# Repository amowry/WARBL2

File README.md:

## WARBL2 is an open-source USB MIDI and BLE MIDI wind controller.

Please see the web site for more info:

https://warbl.xyz

To power the WARBL on, plug into USB or click button 3 (lowest button).

To manually power off the WARBL while under battery power, you can click the reset button (or use a button action assigned in the Configuration Tool, which by default is a long-press of button 3).

For updating the firmware, typical users would just hold down button 1 while plugging the WARBL in to USB and then drag/drop the supplied .uf2 file to the drive named WARBLBOOT. If the WARBL is already plugged in, you can also double-click the reset button to enter the bootloader mode. The most recent flash.uf2 file is located in the build/adafruit.nrf52.warbl2 directory.
 
Advanced users can use the Arduino IDE to modify and upload the code. Modify the code at your own risk and note that while modifying the battery management code won't have dangerous results it could result in reducing the lifespan of the battery.

### How to use WARBL2 with the Arduino IDE:

#### Install Arduino IDE

* Install / run the latest version of the Arduino IDE. [You can download the latest version of the Arduino IDE here](https://www.arduino.cc/en/Main/Software).

* In Linux, the Arduino IDE requires that you be part of the `dialout` group to successfully detect and write to hardware (see [here](https://support.arduino.cc/hc/en-us/articles/4401874331410#ser_open-permission-denied)). If running `id` in a terminal does not list `dialout` as one of the groups your user belongs to, [run `sudo usermod -a -G dialout $USER`](https://support.arduino.cc/hc/en-us/articles/360016495679-Fix-port-access-on-Linux), then log out and back in. Running `id` should now include the `dialout` group.

#### Editing and uploading the WARBL firmware

*  I used the Adafruit ItsyBitsy NRF52840 Express for prototyping WARBL, so the easiest way to set up the IDE is to install the Adafruit boards package, [following the instructions here](https://learn.adafruit.com/adafruit-itsybitsy-nrf52840-express/arduino-support-setup).

* Download the WARBL2 code from this repository (I recommend using the most recent *release* code, *NOT* the current main branch), and move the boards.local.txt file from the "firmware" directory into the directory on your machine that contains the boards.txt file for the Adafruit NR52 boards, typically found here:
   
   * Windows: `C:\Users\(username)\AppData\Local\Arduino15\packages\adafruit\hardware\nrf52\1.6.0` 
   
   * Linux: `/home/(username)/.arduino15/packages/adafruit/hardware/nrf52/1.6.0`
     
   * Mac: ` ~/LibraryArduino15/packages/adafruit/hardware/nrf52/1.5.0/`

*	Now open the warbl2_firmware.ino sketch that you saved in your sketchbook folder.
  
*	In the Tools menu select: Board: > Adafruit nRF52 > WARBL2

*	Next, you’ll need to install libraries included in the sketch that aren’t installed by default. To install them, go to Sketch > Include Library > Manage Libraries, then search for the name of each, one at a time. Then it will give you an option to install each one.

*	Then turn on “show verbose ouput" for both "compile" and "upload" under File > Preferences. Now, click the upload button and check that it compiles without errors. 

*	Then, when it tries to upload, you should see this message at the bottom of the screen:

`Waiting for upload port...`

*	IF the WARBL currently has a "Release" version of the firmware (see below), you'll then have to use a toothpick to double-click the reset button to enter programming mode. The LED pulse in blue and the code should upload, which will take several seconds. If the LED doesn’t light or blinks rapidly, try again. If the IDE stops trying to upload, click “Upload” again, and try double-clicking again. It can take a few tries to get the timing right. If you've loaded a non-release version then the serial CDC port will be active and the firmware upload should proceed without having to first double-click the reset button.

### A few additional notes:
The serial CDC class on WARBL needs to be turned off to make it a USB MIDI class-compliant device. This also means that you won't be able to use the serial monitor in Arduino IDE, and you'll have to double-click the programming button to install firmware (as described above). To turn serial back on, you can comment out the following line in the sketch:

`#define RELEASE //Uncomment for release version (turns off CDC)`

Turning on CDC makes it easier to debug and makes it so uploads should proceed automatically.

Have fun!

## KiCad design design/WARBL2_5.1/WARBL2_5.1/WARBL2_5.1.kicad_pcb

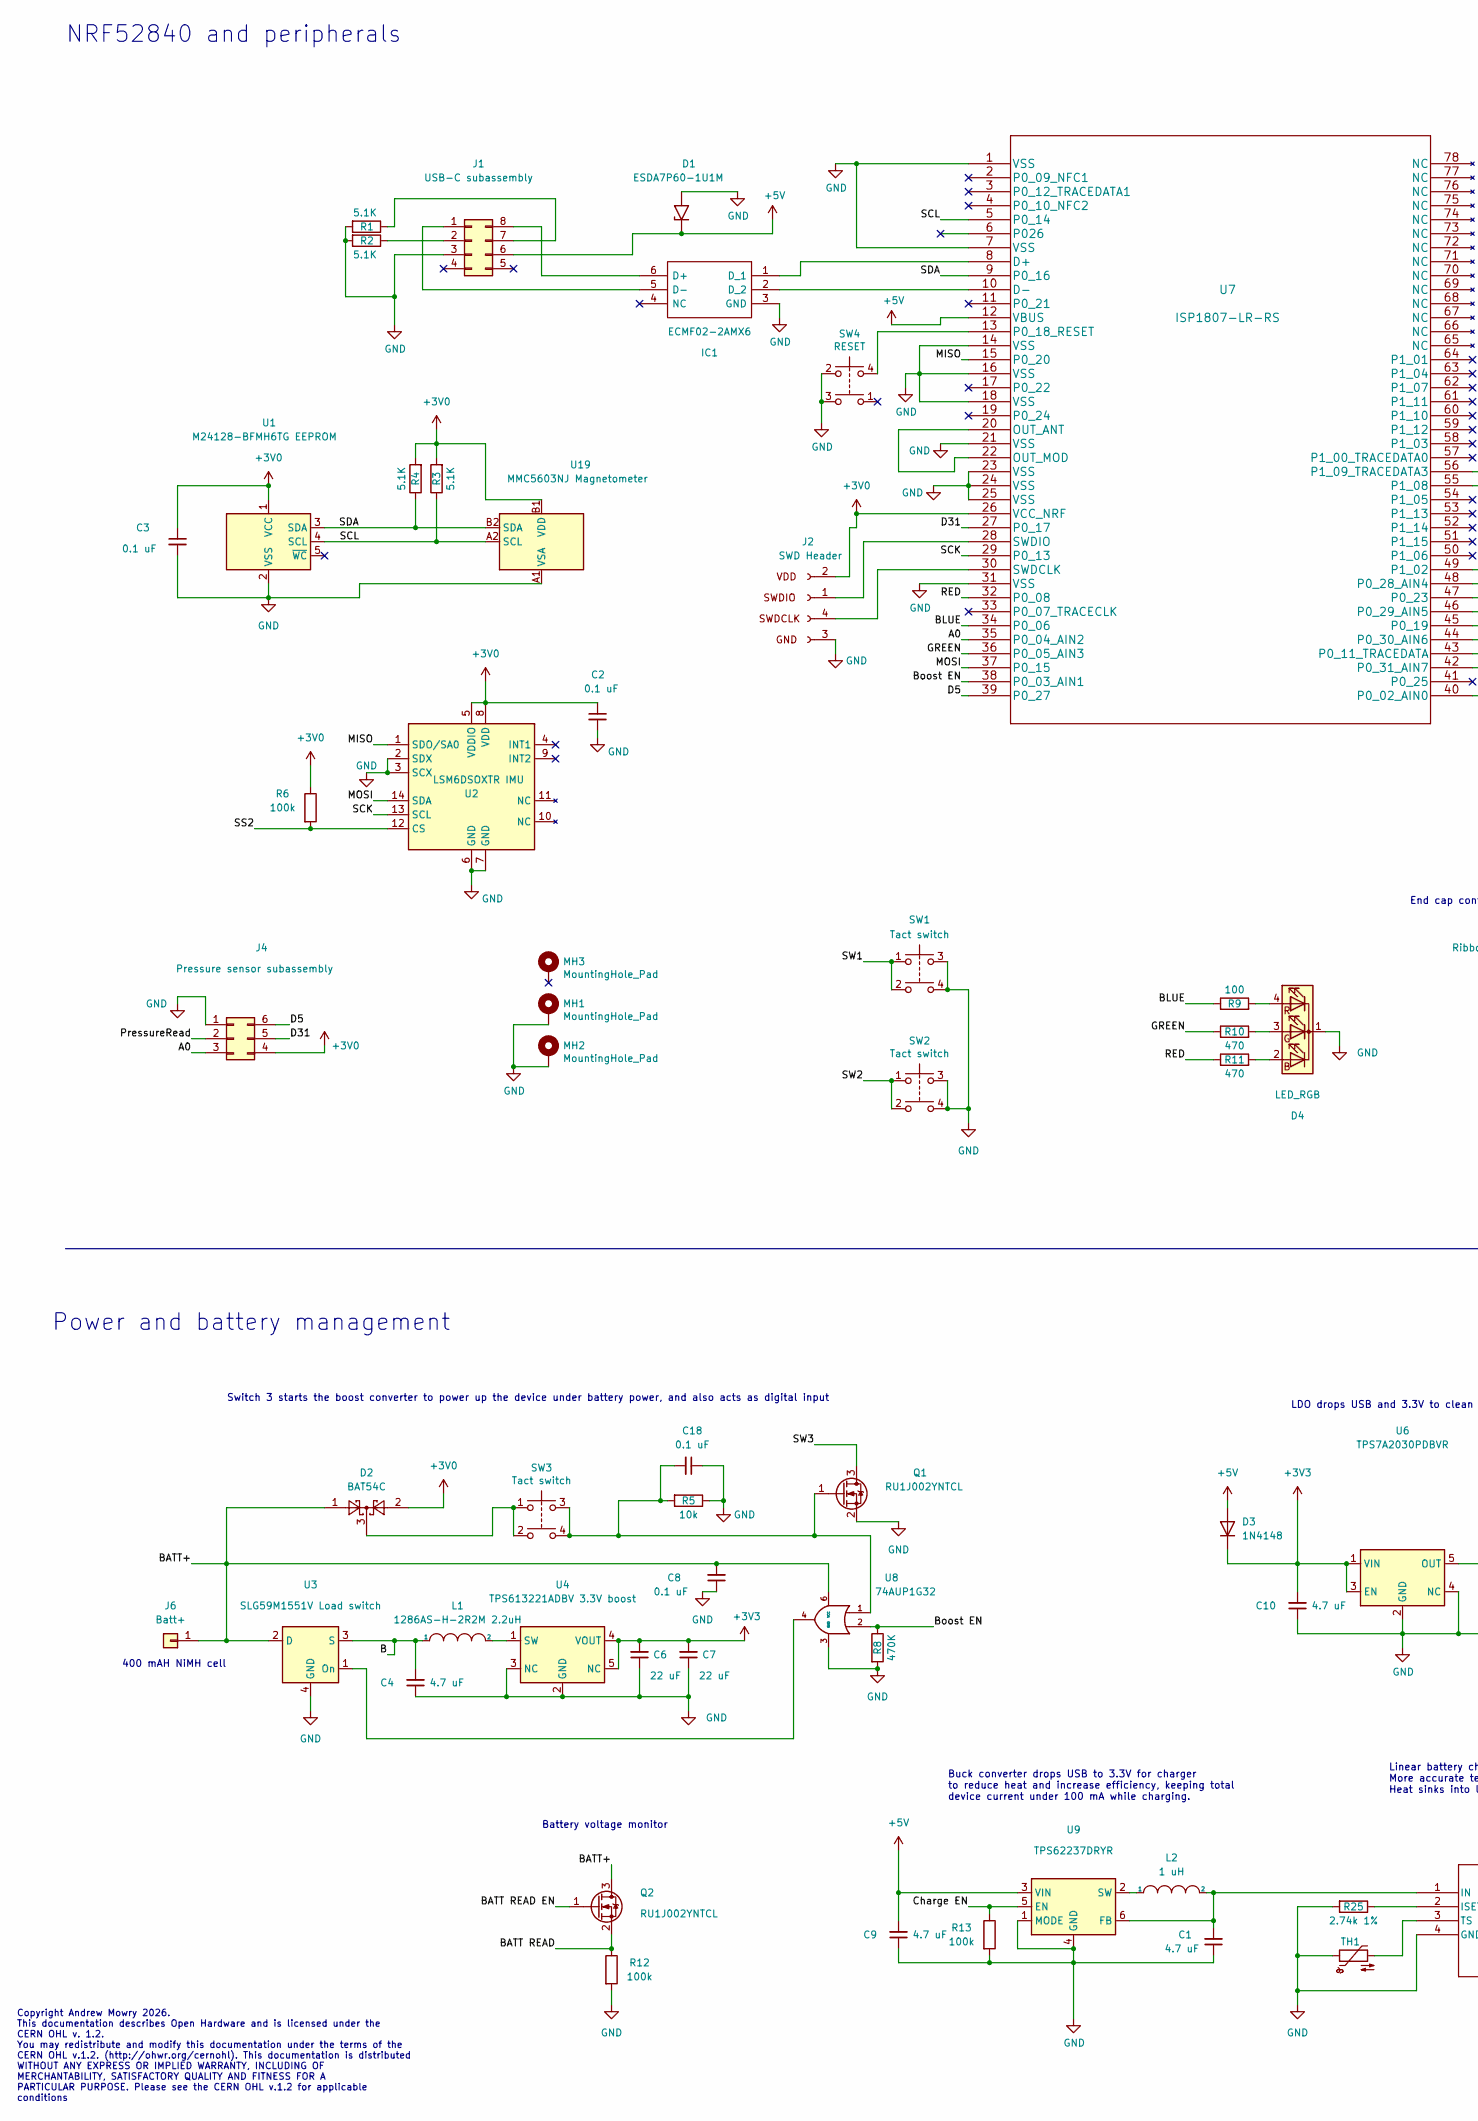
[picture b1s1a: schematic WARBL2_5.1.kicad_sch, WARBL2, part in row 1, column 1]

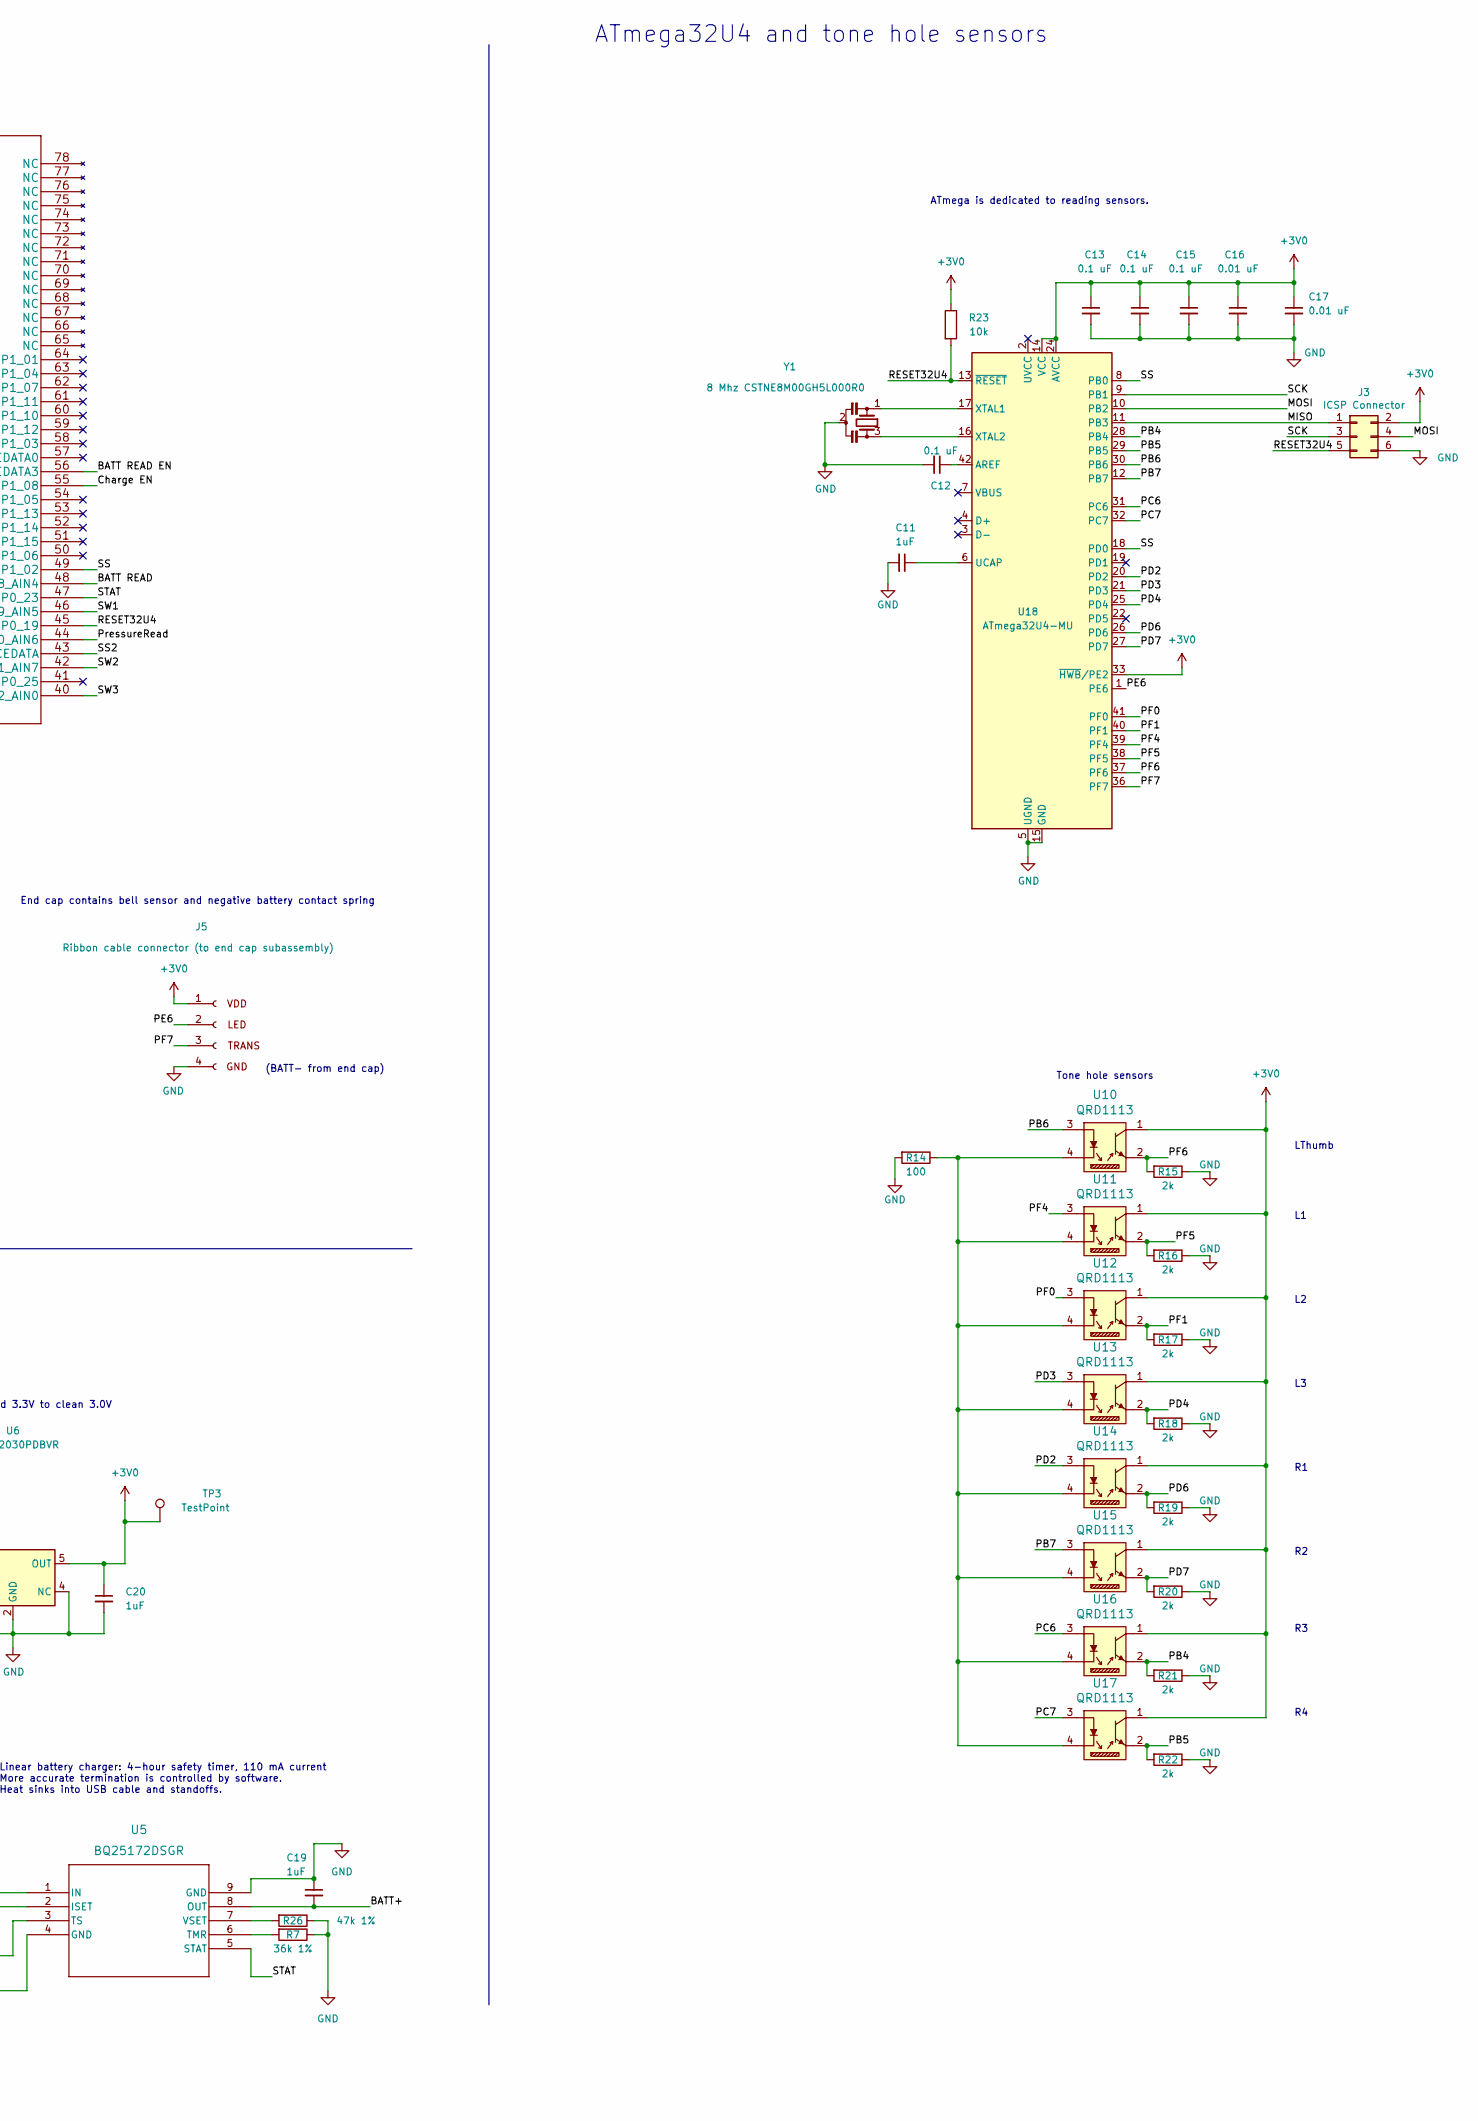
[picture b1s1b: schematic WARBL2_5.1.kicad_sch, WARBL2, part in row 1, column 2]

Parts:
C1, C4, C9, C10: 4.7 uF; C_0603_1608Metric; Mfg Part # C1608X7S1A475K080AC; Digi-Key_PN 445-14258-2-ND
C2, C3, C8, C12, C13, C14, C15, C18: 0.1 uF; C_0603_1608Metric; Mfg Part # CL10F104ZB8NNNC; Digi-Key_PN 1276-1012-2-ND
C6, C7: 22 uF; C_0603_1608Metric; Mfg Part # C1608X5R1A226M080AC; Digi-Key_PN 445-9077-2-ND
C11, C19, C20: 1uF; C_0603_1608Metric; Mfg Part # CL10B105KP8NNNC; Digi-Key_PN 1276-1946-2-ND
C16, C17: 0.01 uF; C_0603_1608Metric; Mfg Part # CL10B103KB8NNNC; Digi-Key_PN 1276-1009-2-ND
D1: ESDA7P60-1U1M; ESDA7P601U1M; Mfg Part # ESDA7P60-1U1M; Digi-Key_PN 497-16253-2-ND
D2: BAT54C; SOT-23; Mfg Part # BAT54C; Digi-Key_PN 1655-BAT54CTR-ND
D3: 1N4148; D_SOD-323; Mfg Part # 1N4148WS; Digi-Key_PN 1655-1N4148WSTR-ND
D4: LED_RGB; LED_LiteOn_LTST-C19HE1WT; Mfg Part # APTF1616SEJ3ZGGVBDC; Digi-Key_PN 754-2166-2-ND
IC1: ECMF02-2AMX6; QFN-6L_STM; Mfg Part # ECMF02-2AMX6; Digi-Key_PN 497-10773-2-ND
J1: USB-C subassembly; PinHeader_2x04_P2.54mm_Vertical; JLCPCB BOM 0
J2: SWD Header; PinHeader_1x04_P2.54mm_Vertical_SMD_Pin1Left; JLCPCB BOM 0
J3: ICSP Connector; SMD_ICSPHeader_Pitch2.54mm; JLCPCB BOM 0
J4: Pressure sensor subassembly; ABPLLND060MGAA3_largepads; JLCPCB BOM 0
J5: Ribbon cable connector (to end cap subassembly); PinHeader_1x04_P2.00mm_Vertical; JLCPCB BOM 0
J6: Batt+; PinHeader_1x01_P1.00mm_Vertical; JLCPCB BOM 0
L1: 1286AS-H-2R2M 2.2uH; INDC2016X120N; Mfg Part # 1286AS-H-2R2M=P2; Digi-Key_PN 490-10605-2-ND
L2: 1 uH; L_0603_1608Metric; Mfg Part # LQM18PZ1R0MCHD; Digi-Key_PN 490-15979-2-ND
MH1, MH2, MH3: MountingHole_Pad; MountingHole__2_56_Pad_small; JLCPCB BOM 0
Q1, Q2: RU1J002YNTCL; SOT-323_SC-70; Mfg Part # RU1J002YNTCL; Digi-Key_PN RU1J002YNTCLTR-ND
R1, R2, R3, R4: 5.1K; R_0603_1608Metric; Mfg Part # ERJ-3EKF5101V; Digi-Key_PN P5.10KHTR-ND
R5, R23: 10k; R_0603_1608Metric; Mfg Part # ERJ-3GEYJ103V; Digi-Key_PN P10KGTR-ND
R6, R12, R13: 100k; R_0603_1608Metric; Mfg Part # ERJ-3GEYJ104V; Digi-Key_PN P100KGTR-ND
R7: 36k 1%; R_0603_1608Metric; Mfg Part # ERJ-3EKF3602V; Digi-Key_PN P36.0KHTR-ND
R8: 470K; R_0603_1608Metric; Mfg Part # ERJ-3GEYJ474V; Digi-Key_PN P470KGTR-ND
R9, R14: 100; R_0603_1608Metric; Mfg Part # ERJ-3GEYJ101V; Digi-Key_PN P100GTR-ND
R10, R11: 470; R_0603_1608Metric; Mfg Part # ERJ-3GEYJ471V; Digi-Key_PN P470GTR-ND
R15, R16, R17, R18, R19, R20, R21, R22: 2k; R_0603_1608Metric; Mfg Part # ERJ-3GEYJ202V; Digi-Key_PN P2.0KGTR-ND
R25: 2.74k 1%; R_0603_1608Metric; Mfg Part # ERJ-3EKF2741V; Digi-Key_PN P2.74KHTR-ND
R26: 47k 1%; R_0603_1608Metric; Mfg Part # ERJ-3EKF4702V; Digi-Key_PN P47.0KHTR-ND
SW1, SW2, SW3: Tact switch; TL3305BF160QG; Mfg Part # PTS647SM50SMTR2LFSTR-ND; Digi-Key_PN PTS647SM50SMTR2LFSTR-ND
SW4: RESET; SW_KMR221GLFS; Mfg Part # KMR211GLFS; Digi-Key_PN 401-1426-2-ND
TH1: NCU18XH103F60RB; R_0603_1608Metric; Mfg Part # NCU18XH103F60RB; Digi-Key_PN 2259-TH11-3H103FTTR-ND
TP3: TestPoint; TestPoint_Pad_D1.0mm; JLCPCB BOM 0
U1: M24128-BFMH6TG EEPROM; UFDFPN5_1P7X1P4_STM; Mfg Part # M24128-BFMH6TG; Digi-Key_PN 497-17565-2-ND
U2: LSM6DSOXTR IMU; LGA-14L_2P5X3X0P83_STM; Mfg Part # LSM6DSOXTR; Digi-Key_PN 497-18367-2-ND
U3: SLG59M1551V Load switch; VLGA-4_2x2.5mm_P1.65mm; Mfg Part # SLG59M1551V; Digi-Key_PN 1827-1074-2-ND
U4: TPS613221ADBV 3.3V boost; DBV0005A_L; Mfg Part # TPS613221ADBVT; Digi-Key_PN 296-49467-2-ND
U5: BQ25172DSGR; WSON8_DSG008A_BQ_TEX; Mfg Part # BQ25172DSGR; Digi-Key_PN 296-BQ25172DSGRTR-ND
U6: TPS7A2030PDBVR; DBV0005A_L; Mfg Part # TPS7A2030PDBVR; Digi-Key_PN 296-TPS7A2030PDBVRTR-ND
U7: ISP1807-LR-RS; Mfg Part # ISP1807-LR-RS; Digi-Key_PN 1786-1019-2-ND
U8: 74AUP1G32; DSF6; Mfg Part # SN74AUP1G32DSFR; Digi-Key_PN 296-27310-2-ND
U9: TPS62237DRYR; DRY0006A; Mfg Part # TPS62237DRYR; Digi-Key_PN 296-39454-2-ND
U10, U11, U12, U13, U14, U15, U16, U17: QRD1113; Reflective_Sensor_QRD1114; Digi-Key_PN QRD1113
U18: ATmega32U4-MU; QFN-44-1EP_7x7mm_P0.5mm_EP5.2x5.2mm; Mfg Part # ATMEGA32U4-MUR; Digi-Key_PN ATMEGA32U4-MURTR-ND
U19: MMC5603NJ Magnetometer; WLP-4_0.86x0.86mm_P0.4mm
Y1: 8 Mhz CSTNE8M00GH5L000R0; CSTNE8M00GH5L000R0_MUR; Mfg Part # CSTNE8M00GH5L000R0; Digi-Key_PN 490-17962-2-ND

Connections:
+3V0: C2.1, C3.1, C13.1, C14.1, C15.1, C16.1, C17.1, C20.1, D2.2, J2.2 (VDD), J3.2, J4.4, J5.1 (VDD), R3.2, R4.2, R6.1, R23.1, TP3.1, U1.1 (VCC), U2.5 (VDDIO), U2.8 (VDD), U6.5 (OUT), U7.26 (VCC_NRF), U10.1, U11.1, U12.1, U13.1, U14.1, U15.1, U16.1, U17.1, U18.14 (VCC), U18.24 (AVCC), U18.33 (~HWB/PE2), U18.34 (VCC), U18.44 (AVCC), U19.B1 (VDD)
+3V3: C6.2, C7.2, C10.2, D3.1 (K), U4.4 (VOUT), U4.5 (NC), U6.1 (VIN), U6.3 (EN)
+5V: C9.2, D1.1 (A1), D3.2 (A), J1.6, U7.12 (VBUS), U9.3 (VIN)
/A0: J4.3, U7.35 (P0_04_AIN2)
/B: C4.2, L1.1, U3.3 (S)
/BATT READ: Q2.2 (S), R12.1, U7.48 (P0_28_AIN4)
/BATT READ EN: Q2.1 (G), U7.56 (P1_09_TRACEDATA3)
/BATT+: C8.2, C19.2, D2.1, J6.1, Q2.3 (D), U3.2 (D), U5.8 (OUT), U8.6 (VCC)
/BLUE: R9.1, U7.34 (P0_06)
/Boost EN: R8.1, U7.38 (P0_03_AIN1), U8.2
/Charge EN: R13.1, U7.55 (P1_08), U9.5 (EN)
/D5: J4.6, U7.39 (P0_27)
/D31: J4.5, U7.27 (P0_17)
/GREEN: R10.1, U7.36 (P0_05_AIN3)
/MISO: J3.1, U2.1 (SDO/SA0), U7.15 (P0_20), U18.11 (PB3)
/MOSI: J3.4, U2.14 (SDA), U7.37 (P0_15), U18.10 (PB2)
/PB4: R21.2, U16.2, U18.28 (PB4)
/PB5: R22.2, U17.2, U18.29 (PB5)
/PB6: U10.3, U18.30 (PB6)
/PB7: U15.3, U18.12 (PB7)
/PC6: U16.3, U18.31 (PC6)
/PC7: U17.3, U18.32 (PC7)
/PD2: U14.3, U18.20 (PD2)
/PD3: U13.3, U18.21 (PD3)
/PD4: R18.2, U13.2, U18.25 (PD4)
/PD6: R19.2, U14.2, U18.26 (PD6)
/PD7: R20.2, U15.2, U18.27 (PD7)
/PE6: J5.2 (SWDIO), U18.1 (PE6)
/PF0: U12.3, U18.41 (PF0)
/PF1: R17.2, U12.2, U18.40 (PF1)
/PF4: U11.3, U18.39 (PF4)
/PF5: R16.2, U11.2, U18.38 (PF5)
/PF6: R15.2, U10.2, U18.37 (PF6)
/PF7: J5.3 (SWDCLK), U18.36 (PF7)
/PressureRead: J4.2, U7.44 (P0_30_AIN6)
/RED: R11.1, U7.32 (P0_08)
/RESET32U4: J3.5, R23.2, U7.45 (P0_19), U18.13 (~RESET)
/SCK: J3.3, U2.13 (SCL), U7.29 (P0_13), U18.9 (PB1)
/SCL: R3.1, U1.4 (SCL), U7.5 (P0_14), U19.A2 (SCL)
/SDA: R4.1, U1.3 (SDA), U7.9 (P0_16), U19.B2 (SDA)
/SS: U7.49 (P1_02), U18.8 (PB0), U18.18 (PD0)
/SS2: R6.2, U2.12 (CS), U7.43 (P0_11_TRACEDATA)
/STAT: U5.5 (STAT), U7.47 (P0_23)
/SW1: SW1.1, SW1.2, U7.46 (P0_29_AIN5)
/SW2: SW2.1, SW2.2, U7.42 (P0_31_AIN7)
/SW3: Q1.3 (D), U7.40 (P0_02_AIN0)
GND: C1.1, C2.2, C3.2, C4.1, C6.1, C7.1, C8.1, C9.1, C10.1, C11.2, C12.2, C13.2, C14.2, C15.2, C16.2, C17.2, C18.1, C19.1, C20.2, D1.2 (A2), D4.1 (K), IC1.3 (GND), J1.3, J2.3 (GND), J3.6, J4.1, J5.4 (GND), MH1.1, MH2.1, Q1.2 (S), R1.2, R2.2, R5.1, R7.1, R8.2, R12.2, R13.2, R14.2, R15.1, R16.1, R17.1, R18.1, R19.1, R20.1, R21.1, R22.1, R25.2, R26.1, SW1.3, SW1.4, SW2.3, SW2.4, SW4.2, SW4.3, TH1.1, U1.2 (VSS), U2.2 (SDX), U2.3 (SCX), U2.6 (GND), U2.7 (GND), U3.4 (GND), U4.2 (GND), U4.3 (NC), U5.4 (GND), U5.9 (GND), U6.2 (GND), U6.4 (NC), U7.1 (VSS), U7.7 (VSS), U7.14 (VSS), U7.16 (VSS), U7.18 (VSS), U7.21 (VSS), U7.23 (VSS), U7.24 (VSS), U7.25 (VSS), U7.31 (VSS), U8.3 (GND), U9.1 (MODE), U9.4 (GND), U18.5 (UGND), U18.15 (GND), U18.23 (GND), U18.35 (GND), U18.43 (GND), U18.45 (GND), U19.A1 (VSA), Y1.2
unnamed: C1.2, L2.2, U5.1 (IN), U9.6 (FB)
unnamed: C11.1, U18.6 (UCAP)
unnamed: C12.1, U18.42 (AREF)
unnamed: C18.2, Q1.1 (G), R5.2, SW3.3, SW3.4, U8.1
unnamed: D2.3, SW3.1, SW3.2
unnamed: D4.2 (BA), R11.2
unnamed: D4.3 (GA), R10.2
unnamed: D4.4 (RA), R9.2
unnamed: IC1.1 (D_1), U7.8 (D+)
unnamed: IC1.2 (D_2), U7.10 (D-)
unnamed: IC1.5 (D-), J1.1
unnamed: IC1.6 (D+), J1.8
unnamed: J1.2, R2.1
unnamed: J1.7, R1.1
unnamed: J2.1 (SWDIO), U7.28 (SWDIO)
unnamed: J2.4 (SWDCLK), U7.30 (SWDCLK)
unnamed: L1.2, U4.1 (SW)
unnamed: L2.1, U9.2 (SW)
unnamed: R7.2, U5.6 (TMR)
unnamed: R14.1, U10.4, U11.4, U12.4, U13.4, U14.4, U15.4, U16.4, U17.4
unnamed: R25.1, U5.2 (ISET)
unnamed: R26.2, U5.7 (VSET)
unnamed: SW4.4, U7.13 (P0_18_RESET)
unnamed: TH1.2, U5.3 (TS)
unnamed: U3.1 (On), U8.4
unnamed: U7.20 (OUT_ANT), U7.22 (OUT_MOD)
unnamed: U18.16 (XTAL2), Y1.3
unnamed: U18.17 (XTAL1), Y1.1

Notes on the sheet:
Battery voltage monitor
Switch 3 starts the boost converter to power up the device under battery power, and also acts as digital input
400 mAH NiMH cell
Power and battery management
Copyright Andrew Mowry 2026. This documentation describes Open Hardware and is licensed under the CERN OHL v. 1.2. You may redistribute and modify this documentation under the terms of the CERN OHL v.1.2. (http://ohwr.org/cernohl). This documentation is distributed WITHOUT ANY EXPRESS OR IMPLIED WA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
(BATT- from end cap)
End cap contains bell sensor and negative battery contact spring
LDO drops USB and 3.3V to clean 3.0V
Buck converter drops USB to 3.3V for charger to reduce heat and increase efficiency, keeping total device current under 100 mA while charging.
ATmega32U4 and tone hole sensors
Linear battery charger: 4-hour safety timer, 110 mA current More accurate termination is controlled by software. Heat sinks into USB cable and standoffs.
NRF52840 and peripherals
Tone hole sensors
ATmega is dedicated to reading sensors.
LThumb

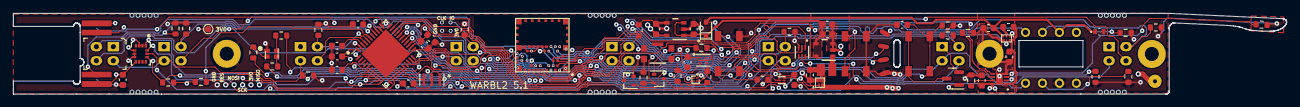
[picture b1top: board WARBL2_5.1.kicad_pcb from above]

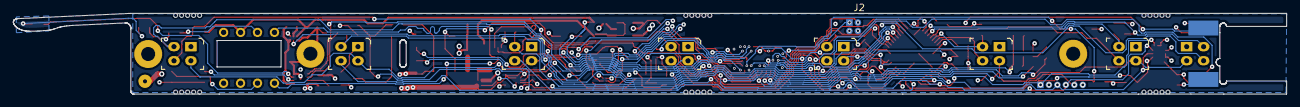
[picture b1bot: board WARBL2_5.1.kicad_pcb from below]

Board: 4 copper layers, 190.8 x 12.1 mm, 94 parts (9 on the bottom side), 75 nets.

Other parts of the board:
84, 84#2, 84#3, 84#4, 84#5, 84#6: (no value)

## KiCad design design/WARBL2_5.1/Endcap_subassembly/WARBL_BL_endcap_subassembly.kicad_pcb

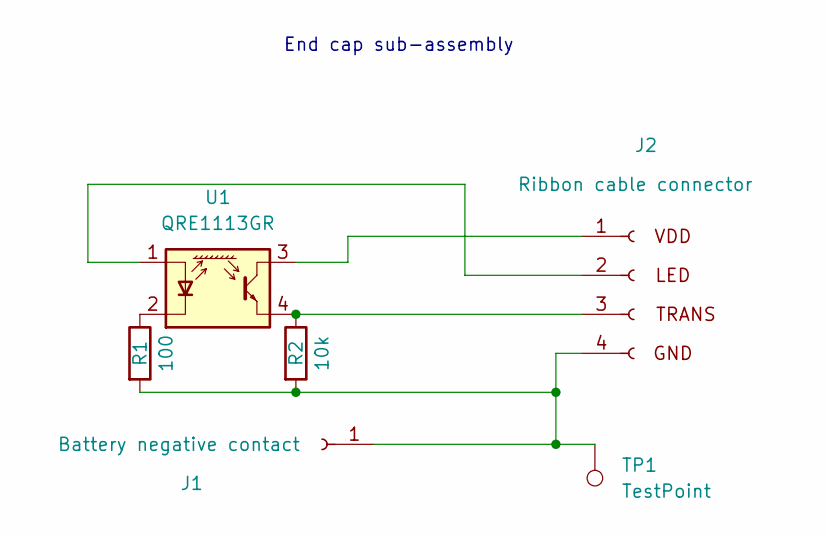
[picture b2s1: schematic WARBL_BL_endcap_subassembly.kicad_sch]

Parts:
J1: Battery negative contact; Batt contact
J2: Ribbon cable connector; Ribbon_connector
R1: 100; R_0603_1608Metric; Mfg Part # ERJ-3GEYJ101V
R2: 10k; R_0603_1608Metric; Mfg Part # ERJ-3GEYJ103V
TP1: TestPoint; Batt_spring_pad
U1: QRE1113GR; SMD4_2P90X3P60_ONS

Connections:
unnamed: J1.1, J2.4 (GND), R1.2, R2.2, TP1.1
unnamed: J2.1 (VDD), U1.3
unnamed: J2.2 (SWDIO), U1.1 (A)
unnamed: J2.3 (SWDCLK), R2.1, U1.4
unnamed: R1.1, U1.2 (K)

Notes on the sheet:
End cap sub-assembly

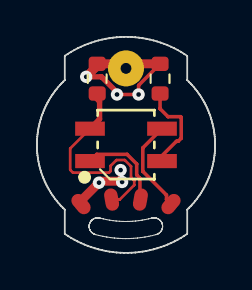
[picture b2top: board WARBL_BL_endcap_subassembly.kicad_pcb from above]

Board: 2 copper layers, 9.9 x 12.0 mm, 6 parts (1 on the bottom side), 5 nets.

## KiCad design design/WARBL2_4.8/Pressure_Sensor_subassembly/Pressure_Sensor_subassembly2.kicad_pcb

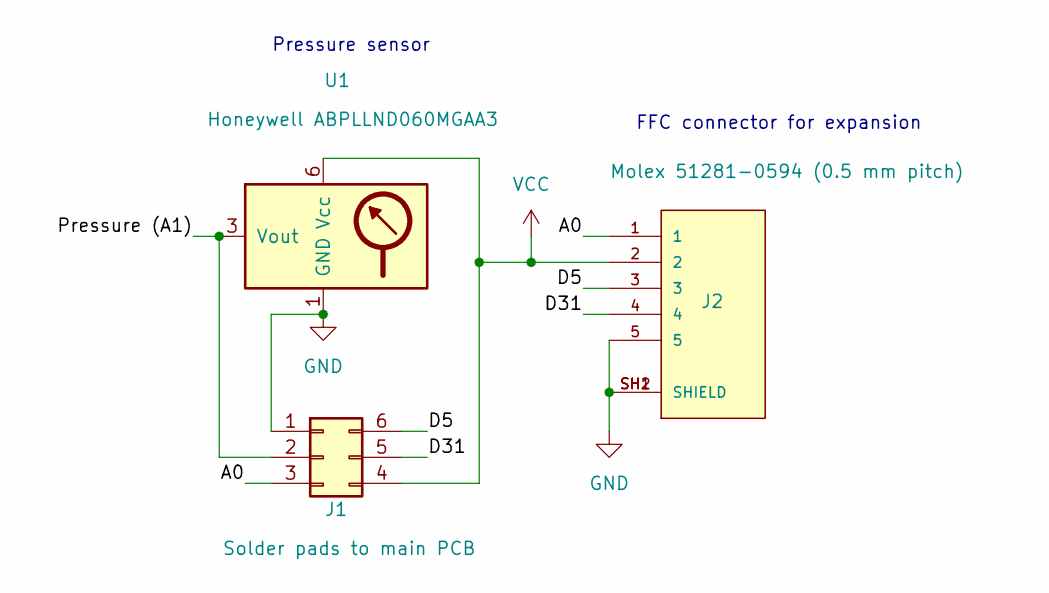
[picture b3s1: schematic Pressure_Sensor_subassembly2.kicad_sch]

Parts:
J1: Solder pads to main PCB; ABPLLND060MGAA3_largepads
J2: Molex 51281-0594 (0.5 mm pitch); MOLEX_51281-0594; PARTREV J
U1: Honeywell ABPLLND060MGAA3; ABPsensor

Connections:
/A0: J1.3, J2.1
/D5: J1.6, J2.3
/D31: J1.5, J2.4
/Pressure (A1): J1.2, U1.3 (Vout)
GND: J1.1, J2.5, J2.SH1 (SHIELD), J2.SH2 (SHIELD), U1.1 (GND)
VCC: J1.4, J2.2, U1.6 (Vcc)

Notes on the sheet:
Pressure sensor
FFC connector for expansion

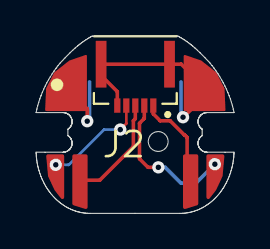
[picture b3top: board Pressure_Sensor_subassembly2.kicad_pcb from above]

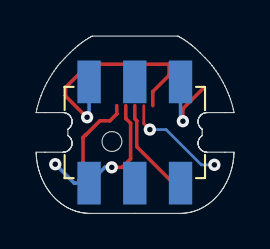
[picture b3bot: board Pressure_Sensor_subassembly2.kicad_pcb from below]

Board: 2 copper layers, 11.0 x 9.8 mm, 3 parts (2 on the bottom side), 6 nets.

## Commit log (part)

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2024-02-17 re-implemented transient filter to be adaptive
2024-02-17 webconfig: increased max for transient filter slider to 100ms
2024-02-19 Cleanup
2024-02-20 Cleanup and added ChangeLog
2024-04-12 Misc fixes
2024-04-24 Misc updates
2024-04-25 Fixed IMU calibration to give gyro time to turn on
2024-05-09 Update Config
2024-05-17 Slight change to basic slide behavior
2024-05-22 Added pitchbend readout to Config Tool
2024-05-23 Changed the custom chart feature so zeros and blanks will produce silent notes.
2024-05-27 Reset the ATmega at startup in case only the NRF52840 has been reset.
2024-06-04 Increased WDT to 10 seconds in case we need to program the ATmega
2024-06-05 More watchdog stuff
2024-06-13 Changed all digitalWrites for LEDs to analogWrites
    ...turns out you can't ever use digitalWrite after analogWrite with this board package.
2024-06-17 Misc. fixes
    0xFF is now used as an "error" code if getNote() fails to find a note in the lookup tables.
2024-06-25 20240625 - defines for EEPROM Addresses and EEPROM Usage Map
2024-06-26 Update Defines.h
    Udated ATMEGA firmware address name
2024-06-26 Update warbl2_firmware.ino
    Udated ATMEGA address define name
2024-06-29 20240629 - MIDI Constant Defines Firmware:
    - Added constants defines for MIDI numerical values
    - Substituted (almost) all MIDI numerical references with constants defines
    Web Config Tool:
    - Added a new file constants.js
    - Modified HTML configure pages to include the new constants.js
    - Substituted (almost) all MIDI numerical references with constants defines
2024-06-29 20240629 - Double Click Button Action
2024-06-30 20240630 - USB/BLE Coexistence in Config Tool
    We keep track of which transport is used to enter communication mode and be consistent with it, avoiding doubled messages.
    Also, proper double messages are now sent without any possibile interruption (sendMidiCouplet())
2024-06-30 20240630 Merge with constant defines and double click
2024-06-30 20240630 Merge with midi_mutex branch
2024-07-01 Added version check for issue #8
2024-07-01 Minox fix in comment
2024-07-01 Default to having double-click turned off if EEPROM is unitialized
2024-07-01 Removed channel mask
2024-07-01 Incremented firmware version and Disabled double-click for earlier versions of WARBL2 as well
2024-07-06 Without parenthesis, sendSettings doesn't work properly
2024-07-06 Semaphore for MIDI couplets
2024-07-08 Added version manager from @MrMep and various minor fixes
2024-07-12 20240712
    - Switched firmware versione to 99 - dev version
    - Added support for default values for new preferences
2024-07-12 Added compiled binaries
2024-07-14 20240714
    - Auto optical calibration
    - Added relative button action
    - Added relative Config tool switch
    - Added relative checks to checkFirmwareVersion
    - removed auto baseline calibration
    - added holeBaseStatus() - contains the previous code of getFingers
2024-07-14 Uploaded binaries
2024-07-14 Fixed mistake in constants
2024-07-15 Fixed typo
2024-07-16 Added automatic reconnect
2024-07-17 Changed disabling of slide
2024-07-17 fixes for slide/vibrato and silent notes
2024-07-18 - Change back fp.holes to fp.holeCovered for clarity - Fixed bug with transient filter and slide - Added half-thumb-in-the-middle option
2024-07-30 Fixed Gaita note and closed pipe behavior
2024-07-30 Changed disconnect method for WARBL2
    Now only disconnecting if a message hasn't been received from WARBL2 for 40 seconds. This avoids spurious disconnects with BLE.
2024-07-30 Added binaries
2024-07-30 More fixes to pitch expression
2024-08-01 Improved disconnect behavior yet again
2024-08-01 Minified constants.js
2024-08-07 Fixed small MIDI note display
    It was sometimes turning off notes prematurely.
2024-08-23 Enabled momentary button behavior for CC
    If momentary switch is turned on, the button will send a CC with a value of 0 when released, for controlling CC switches, e.g. CC64-69.
2024-09-04 Updates for firmware 4.2 release
2024-09-15 Revamped device connection logic, including manual device connect capability
2024-09-16 Reworked of connection logic, adding support for manual device select, which lets you switch easily between multiple connected WARBLs and ensure only the selected one is used
2024-09-16 updated for testing with configureForApp
2024-09-17 updated with support latest app version using configure.html
2024-09-17 put midi.min in configureforapp just in case
2024-09-18 Added service worker related PWA features
2024-09-19 Prepare for PR
2024-09-19 Debugging information for offline service worker
2024-09-19 Bumped cache ID
2024-09-19 Trying another cache pattern
2024-09-19 Trying tool at a /tool subdirectory
2024-09-19 Removed tool directory
2024-09-20 First version of the configuration tool that works offline
2024-09-21 New app icons with more space around the logo
2024-09-22 Only registering service worker on web version
2024-09-23 first pass at new pitch expression override
2024-09-23 slider styling
2024-09-23 minor fixes
2024-09-23 added input pressure visual indicator in the expr override
2024-09-23 cleaned up unnecessary slider handles, added labels. added recv cents for pitchbend
2024-09-23 refinements to pitch expression override defaults. added reset to default command
2024-09-23 update pitch expression with curves for low and high range
2024-09-23 added support for new non-override pitch expression. added notion of center pressure to it. updated webconfig too.
2024-09-23 updated minified versions
2024-09-23 commented prototype
2024-09-23 put expr pressure sliders back up to 0-24 range
2024-09-23 A few changes to Config Tool UI
2024-09-25 moved new pitch expression param init to firmware check area. added support for IMU shake output pressure feature. added support for MPE+ 14 bit channel pressure output option
2024-09-26 added shake pressure mod mode, and fixed up update interval issue for it
2024-09-26 update configureforapp, and commented prototype
2024-09-26 use constants min
2024-09-26 fixed visibility of shake pressure mod for old firmwares
2024-10-04 Updated binaries for 4.3
2024-10-26 fix up baseline and covered hole calibration issues to be adapt to more variety in fingerhole situations. updated firmware version to 44.
2024-10-26 removed some printouts
2024-10-28 A few fixes to new calibration
2024-11-04 Added IMU pitchbend mapping
2024-11-04 Another fix
2024-11-06 Changed IMU pitchbend defaults, clamping, misc fixes
2024-11-22 prevented IMU shake pressure mod from being used if input pressure is zero. This prevents shaking sented unwanted messages when no blowing is even occurring
2024-11-22 Fixed uilleann "custom" vibrato
2024-11-22 Updated binaries
2024-12-20 Hopefully fixed the preset export
2024-12-31 More fixes to preset import/export
2025-01-28 Added an overblow semitones setting
2025-02-13 Firmware 4.4 release
2025-03-03 Fixed bug where IMU pitchbend wasn't being turned off with switch
    Pitchbend of zero wasn't being sent after turning off IMU pitchbend.
2025-03-23 More work on halfhole pitchbend
2025-03-26 Fixed bug in halfhole pitchbend
2025-03-27 Added transverse mouthpiece
2025-03-30 Fixed comments related to Bansuri
2025-03-30 Fixed bansuri chart
2025-08-01 More work on half holing
2025-08-08 Create WARBL_mouthpiece_9.0_mm.stl
    This version is the same but with larger internal passages to aid in clearing MJF powder.
2025-08-09 fixed lack of hysteresis in half holing because of missing initialization state of inTargetRegion
2025-08-11 refinements to hysteresis edge cases on half-holing. added responsive filtering to tonehole raw sensor readings, which cleans up slide, esp with half-holing, doesnt seem to affect responsiveness or a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
2025-08-11 commented out prototype define
2025-08-11 Fixed thumb register order
2025-08-13 4.5 release
2025-09-08 Halfhole fix
    The finger rate wasn't being calculated correctly when the finger was first removed from a covered hole.
2025-11-13 Added end cap
2025-11-13 Removed older mouthpiece design
2026-03-07 Yaw is now the compass direction in which the long-axis of the WARBL is pointing
    ...this isolates yaw from roll so it is much more useful. Also other minor fixes.
2026-03-09 Updated transverse mouthpiece
2026-03-09 Fixed longstanding bug with buttons and momentary mode
2026-03-11 Improved ability for 3rd MIDI device to change presets
    ...by PC messages or CC messages
2026-03-11 Added thumbrest
2026-03-12 Fixed BLE connection interval
    Connection interval was being calculated wrong, and also was not being checked again after renegotiation. Also added another request after a delay to try to force renegotiation from iOS. The Config T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
2026-04-06 Added checksum for validating sensor readings.
    ...and various other changes
2026-04-10 Switched to SPIM2
    It seems more reliable but requires a modification to SPI.cpp.
2026-04-21 Update Config Tool
    for 4.6 firmware release
2026-04-21 iOS preset export Config Tool fix
    and removed old files
2026-04-21 Update manifest
2026-04-22 Another half hole fix
    Sending MIDI note instead of pitch bend while half-holing wasn't working with legato slide mode.
2026-04-23 Improved caching of SoundFont on iOS
2026-04-24 Finally fixed iOS app crashing on pinch zoom
    This has happened forever and it turned out to be the modal overlays, which were set to opacity: 0 instead of being hidden.
    Also improved autoconnect behavior so it keeps trying for several seconds in case the ports are slow to open.
    Also removed the pressure graph because it required a lot of code and I'm not sure it was being used.
2026-04-25 Another connection fix
2026-04-27 Fixed legato slide bug
2026-04-29 Config Tool optimizations
2026-05-02 Updated SoundFont
    ...and a few other misc. fixes
2026-05-15 Added magnetometer support and then rolled it back...
    It turned out there was a large bug in the IMU fusion: The library uses micros() to calculate deltaT for gyro integration, but micros() undercounts by about 25% when it spans tickless sleep (every lo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
2026-05-15 Another IMU tweak to improve deltat more.
2026-05-18 Added build flag for choosing SPIM
2026-05-19 Cleanup, compiled binaries.
    Cleanup
2026-05-22 Various connection issue fixes
2026-05-29 Added UF2
2026-05-29 Binaries
2026-06-01 Legato slide limit and z-index fix
2026-06-02 Added firmware download link to Config Tool
2026-06-04 Fix to tiny console in Config Tool
2026-06-06 Incremented version to 47. Added custom curve option and parameter for the four pressure mappings (CC,Vel,ChPrss,PolyPres). Updated web config to present the new option when on 4.7 and above.
2026-06-09 Update Battery_management.ino
    Added a dummy SAADC read for the battery to let the reference settle.
2026-06-15 Added patch display to Config Tool
2026-06-15 Releasing 4.7
2026-06-16 added Duduk fingering
2026-06-16 missed a few things with fingering added
2026-06-16 updated constants.min.js
2026-06-16 Updated service worker
2026-06-16 Disabled duduk for older firmware

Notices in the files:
parts and their libraries:
Copyright 2021 Accelerated Designs. All rights reserved.
